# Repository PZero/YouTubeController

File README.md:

# YouTubeController

Controller fisico per YouTube su iPad: **una sola manopola, che si gira e si preme**, in una scatola stampata in 3D, collegati via Bluetooth a una **PWA** che cerca e riproduce i video.

- **Manopola**: avanti / indietro nel video, con passo che dipende dalla velocità di rotazione (fine / medio / veloce).
- **Pressione della manopola**: play / pausa; pressione media per il loop A-B tra due punti del video.
- **Anello di luce** attorno alla manopola e **vibrazione** per confermare i comandi senza guardare.

> Stato: in sviluppo. Il controller funziona già come tastiera Bluetooth con l'iPad (firmware v0.1.3: manopola, gesti, anello LED, vibrazione, autospegnimento); PWA 1.1.4; scatola V1 pronta da stampare. PCB per JLCPCB progettato (`pcb/`), ordine rimandato.
> Dettagli aggiornati in [`docs/STATO.md`](docs/STATO.md).

## Come funziona

```
 Manopola + pulsante ──► ESP32-S3 (firmware) ══ Bluetooth LE ══► iPad
                         si presenta come                       PWA in Safari / Home
                         TASTIERA BLE (HID)                     legge i tasti e comanda
                                                                il player YouTube (IFrame API)
```

Safari su iPadOS non supporta Web Bluetooth: per questo il controller si presenta come una normale **tastiera Bluetooth** e la PWA ascolta gli eventi tastiera. La velocità della manopola la misura il firmware, che invia un tasto diverso per ogni livello; la PWA somma gli scatti e fa un solo salto quando smetti di girare.

## La PWA

**Indirizzo:** https://pzero.github.io/YouTubeController/ (aprire in Safari sull'iPad → Condividi → *Aggiungi a Home*).

- Ricerca video (YouTube Data API v3, con la **propria chiave API** inserita nelle Impostazioni: resta solo sul dispositivo) o link/ID incollato.
- Preferiti salvati sul dispositivo, con punti del loop A-B e ultima posizione; esporta/importa in JSON.
- Seek a tre velocità con indicatore della posizione di arrivo; loop A-B; schermo pieno automatico al play.
- Sezione *Controller* nelle Impostazioni: gesti, aggiornamento firmware, WiFi.

Dettagli: [`app/README.md`](app/README.md).

### Tasti (inviati dal controller, provabili con qualsiasi tastiera)

| Comando | Tasto |
|---|---|
| Indietro / avanti, passo fine (1 s) | ← / → |
| Passo medio (5 s) | Shift + ← / → |
| Passo veloce (30 s) | Alt + ← / → |
| Play / pausa | Spazio |
| Loop A-B (1ª = A, 2ª = B e avvio, 3ª = cancella) | L |

Riferimento unico: [`app/js/keymap.js`](app/js/keymap.js).

### Gesti del controller

| Gesto | Effetto |
|---|---|
| Rotazione lenta / media / veloce | passo fine / medio / veloce |
| Pressione breve (< 0,7 s) | play / pausa |
| Pressione media (0,7–2 s) | loop A-B |
| Pressione 10 s / 2 s | standby / risveglio |
| Pulsante premuto + 5 scatti avanti | modalità aggiornamento firmware (OTA) |
| Pulsante premuto + 5 scatti indietro | azzera il WiFi di casa |

## Elettronica

| Componente | Ruolo |
|---|---|
| ESP32-S3 SuperMini | BLE HID tastiera, WiFi per gli aggiornamenti OTA |
| Encoder EC11 con albero zigrinato | manopola |
| Pulsante integrato nell'encoder | play / pausa, loop, gesti |
| Modulo TP4056 USB-C con protezione | ricarica (0,5 A) della 18650 |
| Batteria Li-ion 18650 | alimentazione |
| Anello WS2812B 16 LED (Ø45/Ø33) | alone di luce attorno alla manopola |
| Modulo vibrazione (motore a moneta) | conferma dei gesti |

Schema dei collegamenti, GPIO, consumi e piano OTA: [`firmware/README.md`](firmware/README.md).
Schedina millefori di interfaccia (layout, piste, ordine di saldatura): [`firmware/millefori/`](firmware/millefori/README.md).
Circuito stampato per JLCPCB (Gerber, BOM, CPL): [`pcb/`](pcb/AVANZAMENTO.md).
Lista componenti con costi e alternative: [`docs/BOM.md`](docs/BOM.md).

**Aggiornamenti del firmware:** primo caricamento via USB (con la batteria scollegata), poi via WiFi (OTA): il firmware è compilato da GitHub Actions e pubblicato nelle *Releases*; con il gesto di aggiornamento il controller lo scarica da solo. Nessuna password nel firmware: la rete del controller e il WiFi di casa si configurano sulla scheda.

## Scatola

Modello parametrico **OpenSCAD** in [`enclosure/`](enclosure/): scocca, fondo e un **portaschede** intercambiabile avvitato al fondo che porta l'elettronica (se cambia un componente si ristampa solo quello). Stampa su Bambu Lab A1 mini (piatto 180×180) in più piatti.

| | |
|---|---|
|  |  |
|  |  |
|  | |

Tutte le misure condivise tra elettronica e scatola, con fonte e affidabilità: [`enclosure/dimensioni.md`](enclosure/dimensioni.md).

## Struttura del repository

| Cartella / file | Contenuto |
|---|---|
| `app/` | PWA (pubblicata su GitHub Pages); `app/test/` pagina di prova tastiera |
| `firmware/` | firmware ESP32 e documentazione elettronica |
| `enclosure/` | modello 3D OpenSCAD e quote |
| `docs/STATO.md` | stato attuale e prossimi passi |
| `docs/DECISIONI.md` | registro delle decisioni con motivazione |
| `docs/REQUISITI.md`, `docs/BOM.md` | requisiti e componenti |
| `docs/render/`, `docs/foto/` | render della scatola e foto dei componenti |

## Sicurezza

Repository pubblico: **nessuna chiave o password** nei file. La chiave API YouTube sta solo nelle impostazioni della PWA sul dispositivo; le credenziali WiFi solo nella memoria del controller.

## Licenza

[MIT](LICENSE) per tutto il progetto: codice (PWA e firmware), modello 3D e documentazione. Su MakerWorld il modello 3D è pubblicato con licenza CC BY 4.0.

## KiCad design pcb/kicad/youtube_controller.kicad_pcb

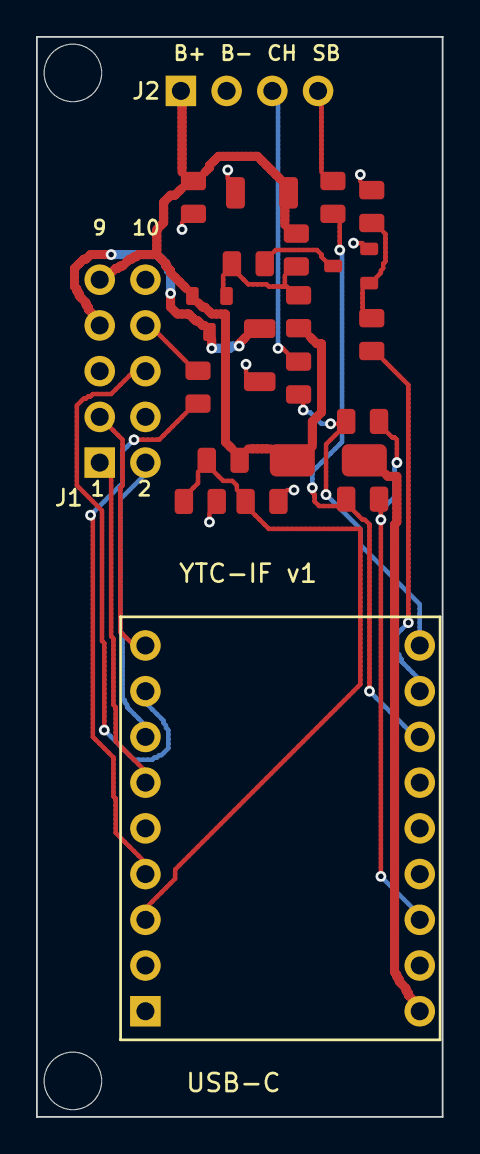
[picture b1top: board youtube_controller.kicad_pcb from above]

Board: 2 copper layers, 22.5 x 60.0 mm, 24 parts (0 on the bottom side), 20 nets.

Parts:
C1, C3: 100uF; C_1206
C2, C4, C5: 100nF; C_0805
D1: SS14; D_SMA
H1, H2: M3; M3_HOLE
J1: scocca 2x5 P2.54; HDR_2x5
J2: TP4056 1x4 P2.54; HDR_1x4
Q1: AO3401A; SOT-23
Q2: MMBT3904; SOT-23
R1: 4.7k; R_0805
R2, R4, R6, R8: 10k; R_0805
R3: 2.2k; R_0805
R5: 330; R_0805
R7, R9: 100k; R_0805
R10, R11: 220k; R_0805
SM: ESP32-S3 SuperMini; SM_SUPERMINI

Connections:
3V3: R7.2, R9.2, SM.H3
5V: D1.1, SM.H1
B_Q1: C5.1, Q1.1, R3.2, R4.2
B_Q2: Q2.1, R1.2, R2.1
CHRG: J2.3, R6.1
C_Q2: Q2.3, R3.1
DI: J1.8, R5.2
ENC_A: J1.1, SM.B6
ENC_B: J1.2, SM.B7
GND: C1.2, C2.2, C3.2, C4.2, J1.4, J1.10, J2.2, Q2.2, R2.2, R11.2, SM.H2
GPIO1: C2.1, R10.2, R11.1, SM.B3
GPIO2: R5.1, SM.B4
GPIO8: R6.2, R7.1, SM.H9
GPIO9: R1.1, SM.H8
GPIO10: R8.2, R9.1, SM.H7
LEDP: C1.1, J1.7, Q1.3
STDBY: J2.4, R8.1
SW: J1.3, SM.B9
VBAT: C3.1, C4.1, C5.2, D1.2, J1.9, J2.1, Q1.2, R4.1, R10.1
VIB_IN: J1.6, SM.B8

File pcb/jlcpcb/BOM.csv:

Comment,Designator,Footprint,LCSC Part #
100uF,C1,C_1206,C15008
100nF,C2,C_0805,C49678
100uF,C3,C_1206,C15008
100nF,C4,C_0805,C49678
100nF,C5,C_0805,C49678
SS14,D1,D_SMA,C2480
AO3401A,Q1,SOT-23,C15127
MMBT3904,Q2,SOT-23,C20526
4.7k,R1,R_0805,C17673
10k,"R2,R4,R6,R8",R_0805,C17414
2.2k,R3,R_0805,C17520
330,R5,R_0805,C17630
100k,"R7,R9",R_0805,C149504
220k,"R10,R11",R_0805,C17556

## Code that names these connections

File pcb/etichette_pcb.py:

# -*- coding: utf-8 -*-
# Serigrafia e ordine di instradamento (eseguito dentro genera_pcb.py)
ROUTE_ORDER = ["GND", "SW", "ENC_A", "ENC_B", "VIB_IN", "5V", "VBAT", "LEDP", "B_Q1", "C_Q2", "B_Q2", "GPIO9", "DI", "GPIO2", "GPIO1",
               "3V3", "GPIO8", "GPIO10", "CHRG", "STDBY"]
SILK = []

SILK = [("USB-C", 8.2, 1.9, 0, 1.0), ("YTC-IF v1", 7.8, 30.2, 0, 1.0),
        ("J1", 0.9, 34.4, 0, 0.9), ("1", 2.9, 34.9, 0, 0.8), ("2", 5.5, 34.9, 0, 0.8), ("10", 5.2, 49.4, 0, 0.8), ("9", 3.0, 49.4, 0, 0.8),
        ("J2", 5.2, 57.0, 0, 0.9),
        ("B+", 7.5, 59.1, 0, 0.8), ("B-", 10.1, 59.1, 0, 0.8), ("CH", 12.7, 59.1, 0, 0.8), ("SB", 15.2, 59.1, 0, 0.8)]
# contorno SuperMini (4,65..22,65 x 4,28..27,78), solo serigrafia
RECTS = [(4.65, 4.28, 22.4, 27.78)]
